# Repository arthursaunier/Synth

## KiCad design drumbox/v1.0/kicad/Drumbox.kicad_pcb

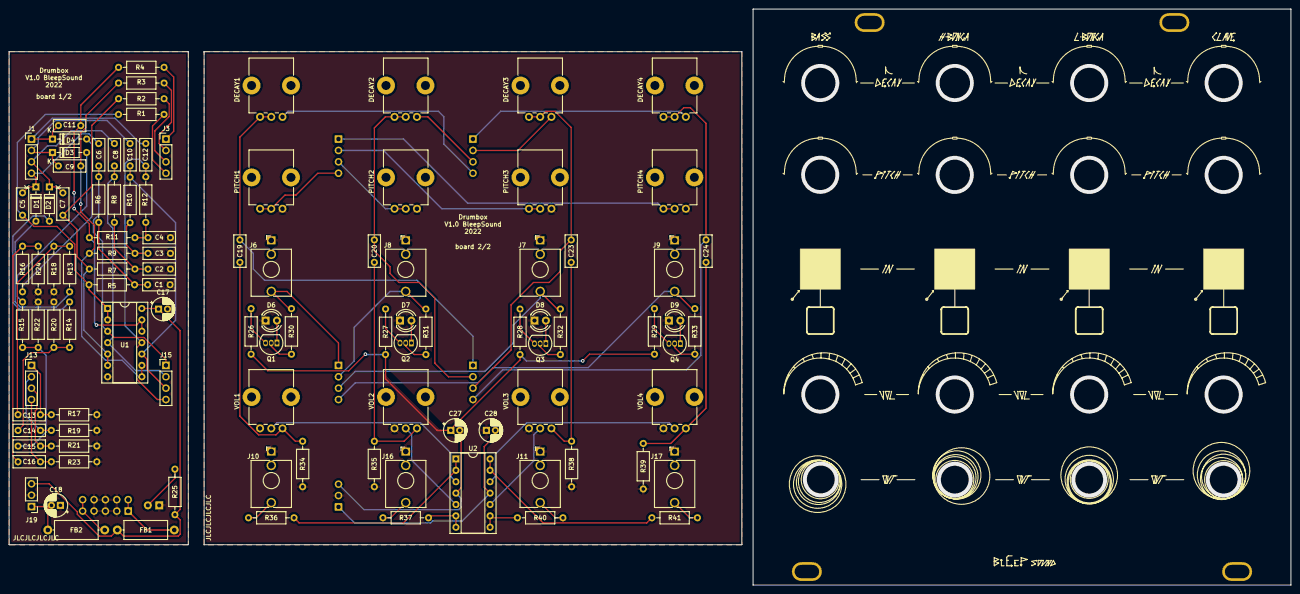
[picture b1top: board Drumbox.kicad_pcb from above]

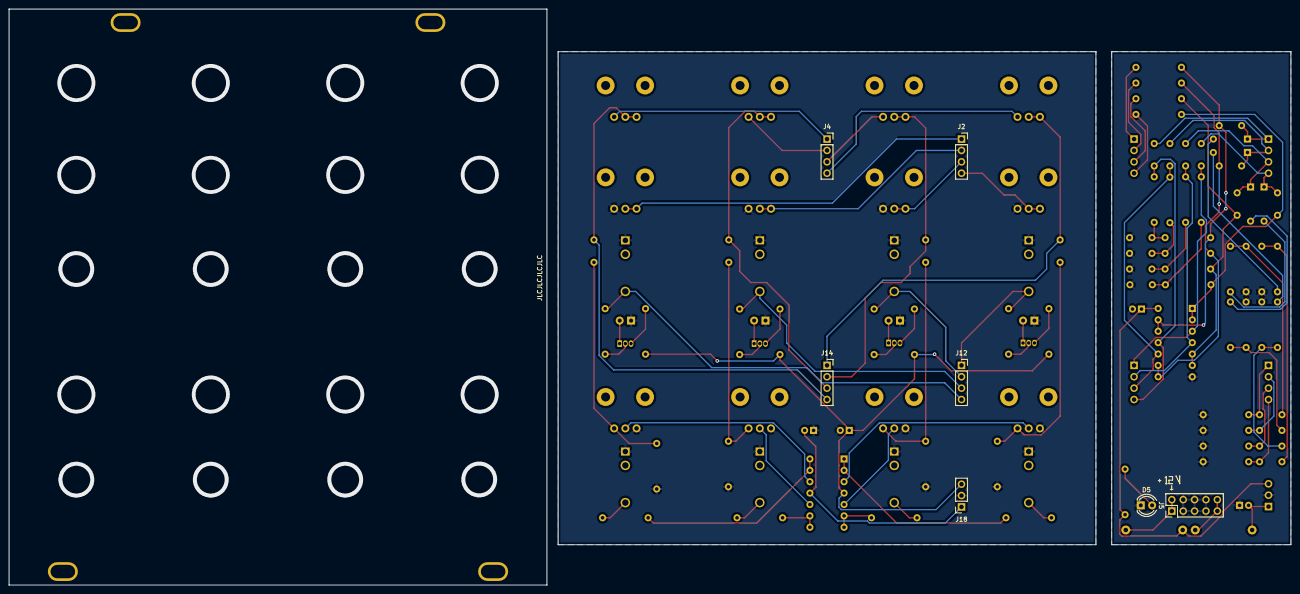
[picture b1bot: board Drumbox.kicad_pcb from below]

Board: 2 copper layers, 286.0 x 128.5 mm, 113 parts (7 on the bottom side), 66 nets.

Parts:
C1, C13: 150nF; C_Disc_D7.0mm_W2.5mm_P5.00mm
C2, C14: 33nF; C_Disc_D7.0mm_W2.5mm_P5.00mm
C3, C15: 39nF; C_Disc_D7.0mm_W2.5mm_P5.00mm
C4: 56nF; C_Disc_D7.0mm_W2.5mm_P5.00mm
C5, C6: 47nF; C_Disc_D7.0mm_W2.5mm_P5.00mm
C7, C8: 10nF; C_Disc_D7.0mm_W2.5mm_P5.00mm
C9, C10: 12nF; C_Disc_D7.0mm_W2.5mm_P5.00mm
C11, C12: 1.5nF; C_Disc_D7.0mm_W2.5mm_P5.00mm
C16: 4.7nF; C_Disc_D7.0mm_W2.5mm_P5.00mm
C17, C18: 10µ; CP_Radial_D5.0mm_P2.00mm
C19, C20, C23, C24: .1µF; C_Disc_D7.0mm_W2.5mm_P5.00mm
C27, C28: 100n; CP_Radial_D5.0mm_P2.00mm
D1, D2, D3, D4: 1N4148; D_DO-35_SOD27_P7.62mm_Horizontal
D5: LED-12V; LED_D4.0mm
D6: LED1; LED_D4.0mm
D7: LED2; LED_D4.0mm
D8: LED3; LED_D4.0mm
D9: LED4; LED_D4.0mm
DECAY1, DECAY2, DECAY3, DECAY4: 470k; Potentiometer_Bourns_PTV09A-1_Single_Vertical
FB1, FB2: 10R; L_Axial_L9.5mm_D4.0mm_P12.70mm_Horizontal_Fastron_SMCC
J1, J3, J13, J15: Conn_01x04_Male; PinHeader_1x04_P2.54mm_Vertical
J2, J4, J12, J14: Conn_01x04_Female; PinSocket_1x04_P2.54mm_Vertical
J5: Power Input; PinHeader_2x05_P2.54mm_Vertical
J6: Bass IN; Jack_3.5mm_QingPu_WQP-PJ398SM_Vertical_CircularHoles
J7: LBonga IN; Jack_3.5mm_QingPu_WQP-PJ398SM_Vertical_CircularHoles
J8: HBonga IN; Jack_3.5mm_QingPu_WQP-PJ398SM_Vertical_CircularHoles
J9: Clave IN; Jack_3.5mm_QingPu_WQP-PJ398SM_Vertical_CircularHoles
J10: Bass OUT; Jack_3.5mm_QingPu_WQP-PJ398SM_Vertical_CircularHoles
J11: LBonga OUT; Jack_3.5mm_QingPu_WQP-PJ398SM_Vertical_CircularHoles
J16: HBonga OUT; Jack_3.5mm_QingPu_WQP-PJ398SM_Vertical_CircularHoles
J17: Clave OUT; Jack_3.5mm_QingPu_WQP-PJ398SM_Vertical_CircularHoles
J18: Conn_01x03_Female; PinSocket_1x03_P2.54mm_Vertical
J19: Conn_01x03_Male; PinHeader_1x03_P2.54mm_Vertical
PITCH1, PITCH2, PITCH3, PITCH4: 10k; Potentiometer_Bourns_PTV09A-1_Single_Vertical
Q1, Q2, Q3, Q4: 2N3904; TO-92_Inline
R1, R2, R3, R4: 150k; R_Axial_DIN0207_L6.3mm_D2.5mm_P10.16mm_Horizontal
R5, R6, R7, R8, R9, R10, R11, R12: 68k; R_Axial_DIN0207_L6.3mm_D2.5mm_P10.16mm_Horizontal
R13, R14, R15, R16: 27k; R_Axial_DIN0207_L6.3mm_D2.5mm_P10.16mm_Horizontal
R17, R19, R21, R23: 12k; R_Axial_DIN0207_L6.3mm_D2.5mm_P10.16mm_Horizontal
R18, R20, R22, R24, R30, R31, R32, R33: 47k; R_Axial_DIN0207_L6.3mm_D2.5mm_P10.16mm_Horizontal
R25: 2.2k; R_Axial_DIN0207_L6.3mm_D2.5mm_P10.16mm_Horizontal
R26, R27, R28, R29, R36, R37, R40, R41: 1k; R_Axial_DIN0207_L6.3mm_D2.5mm_P10.16mm_Horizontal
R34, R35, R38, R39: 1M; R_Axial_DIN0207_L6.3mm_D2.5mm_P10.16mm_Horizontal
U1: 4011; DIP-14_W7.62mm_Socket
U2: TL074; DIP-14_W7.62mm_Socket
VOL1, VOL2, VOL3, VOL4: 10k; Potentiometer_Bourns_PTV09A-1_Single_Vertical

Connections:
+12V: C17.1, C27.1, FB1.1, J18.3, J19.3, R25.1, R26.1, R27.1, R28.1, R29.1, U1.14 (VDD), U2.4 (V+)
-12V: C18.2, C28.2, FB2.1, J18.1, J19.1, U2.11 (V-)
DEIn1: DECAY1.1, J3.4, J4.4, R1.1
DEIn2: DECAY2.1, J3.3, J4.3, R2.1
DEIn3: DECAY3.1, J3.2, J4.2, R3.1
DEIn4: DECAY4.1, J3.1, J4.1, R4.1
GND: C1.2, C2.2, C3.2, C4.2, C17.2, C18.1, C27.2, C28.1, D5.1 (K), D6.1 (K), D7.1 (K), D8.1 (K), D9.1 (K), J5.3, J5.4, J5.5, J5.6, J5.7, J5.8, J6.S, J7.S, J8.S, J9.S, J10.S, J11.S, J16.S, J17.S, J18.2, J19.2, PITCH1.1, PITCH2.1, PITCH3.1, PITCH4.1, R17.2, R18.1, R19.2, R20.1, R21.2, R22.1, R23.2, R24.1, R34.2, R35.2, R38.2, R39.2, U1.7 (VSS), VOL1.3, VOL2.3, VOL3.3, VOL4.3
In1: C13.1, J6.T, J12.1, J13.1, R17.1, R30.1
In2: C14.1, J8.T, J12.2, J13.2, R19.1, R31.1
In3: C15.1, J7.T, J12.3, J13.3, R21.1, R32.1
In4: C16.1, J9.T, J12.4, J13.4, R23.1, R33.1
unnamed: C1.1, R5.1, R6.2
unnamed: C2.1, R7.1, R8.2
unnamed: C3.1, R9.1, R10.2
unnamed: C4.1, R11.1, R12.2
unnamed: C5.1, R1.2, R5.2, U1.1, U1.2
unnamed: C7.1, R2.2, R7.2, U1.5, U1.6
unnamed: C9.1, R3.2, R9.2, U1.8, U1.9
unnamed: C11.1, R4.2, R11.2, U1.12, U1.13
unnamed: C13.2, R13.1, R18.2
unnamed: C14.2, R14.1, R20.2
unnamed: C15.2, R15.1, R22.2
unnamed: C16.2, R16.1, R24.2
unnamed: C19.2, R34.1, VOL1.1
unnamed: C20.2, R35.1, VOL2.1
unnamed: C23.2, R38.1, VOL3.1
unnamed: C24.2, R39.1, VOL4.1
unnamed: D1.2 (A), R13.2
unnamed: D2.2 (A), R14.2
unnamed: D3.2 (A), R15.2
unnamed: D4.2 (A), R16.2
unnamed: D5.2 (A), R25.2
unnamed: D6.2 (A), Q1.1 (E)
unnamed: D7.2 (A), Q2.1 (E)
unnamed: D8.2 (A), Q3.1 (E)
unnamed: D9.2 (A), Q4.1 (E)
unnamed: FB1.2, J5.1, J5.2
unnamed: FB2.2, J5.9, J5.10
unnamed: Q1.2 (B), R30.2
unnamed: Q1.3 (C), R26.2
unnamed: Q2.2 (B), R31.2
unnamed: Q2.3 (C), R27.2
unnamed: Q3.2 (B), R32.2
unnamed: Q3.3 (C), R28.2
unnamed: Q4.2 (B), R33.2
unnamed: Q4.3 (C), R29.2
unnamed: R36.2, U2.1, U2.2 (-)
unnamed: R37.2, U2.6 (-), U2.7
unnamed: R40.2, U2.8, U2.9 (-)
unnamed: R41.2, U2.13 (-), U2.14
unnamed: U2.3 (+), VOL1.2
unnamed: U2.5 (+), VOL2.2
unnamed: U2.10 (+), VOL3.2
unnamed: U2.12 (+), VOL4.2
O1: C6.2, C19.1, DECAY1.2, DECAY1.3, J14.1, J15.1, R6.1, U1.3
O2: C8.2, C20.1, DECAY2.2, DECAY2.3, J14.2, J15.2, R8.1, U1.4
O3: C10.2, C23.1, DECAY3.2, DECAY3.3, J14.3, J15.3, R10.1, U1.10
O4: C12.2, C24.1, DECAY4.2, DECAY4.3, J14.4, J15.4, R12.1, U1.11
Out1: J10.T, R36.1
Out2: J16.T, R37.1
Out3: J11.T, R40.1
Out4: J17.T, R41.1
PIOut1: C5.2, C6.1, D1.1 (K), J1.4, J2.4, PITCH1.2, PITCH1.3
PIOut2: C7.2, C8.1, D2.1 (K), J1.3, J2.3, PITCH2.2, PITCH2.3
PIOut3: C9.2, C10.1, D3.1 (K), J1.2, J2.2, PITCH3.2, PITCH3.3
PIOut4: C11.2, C12.1, D4.1 (K), J1.1, J2.1, PITCH4.2, PITCH4.3

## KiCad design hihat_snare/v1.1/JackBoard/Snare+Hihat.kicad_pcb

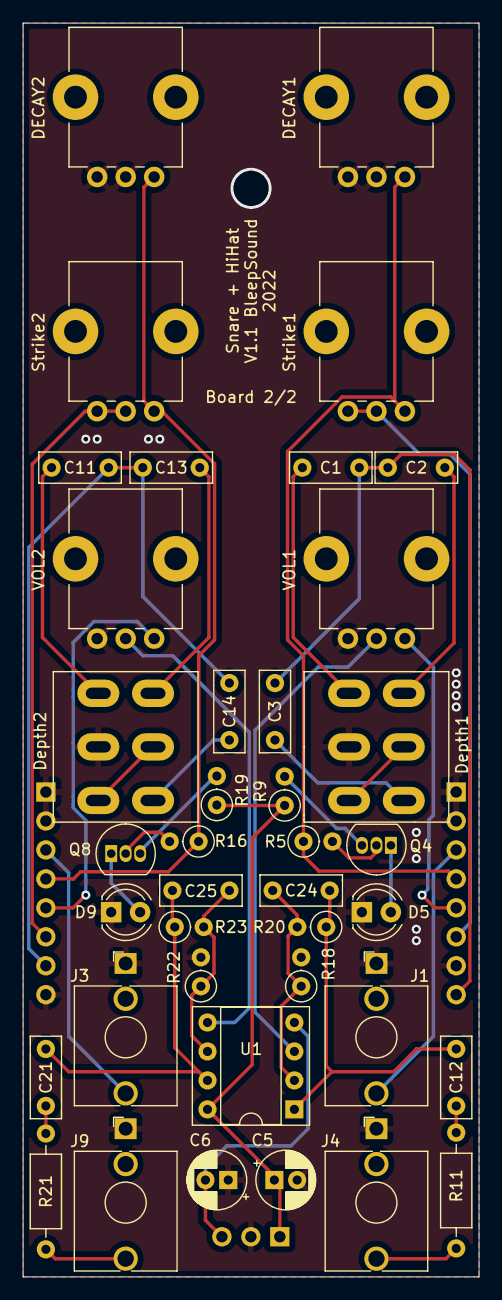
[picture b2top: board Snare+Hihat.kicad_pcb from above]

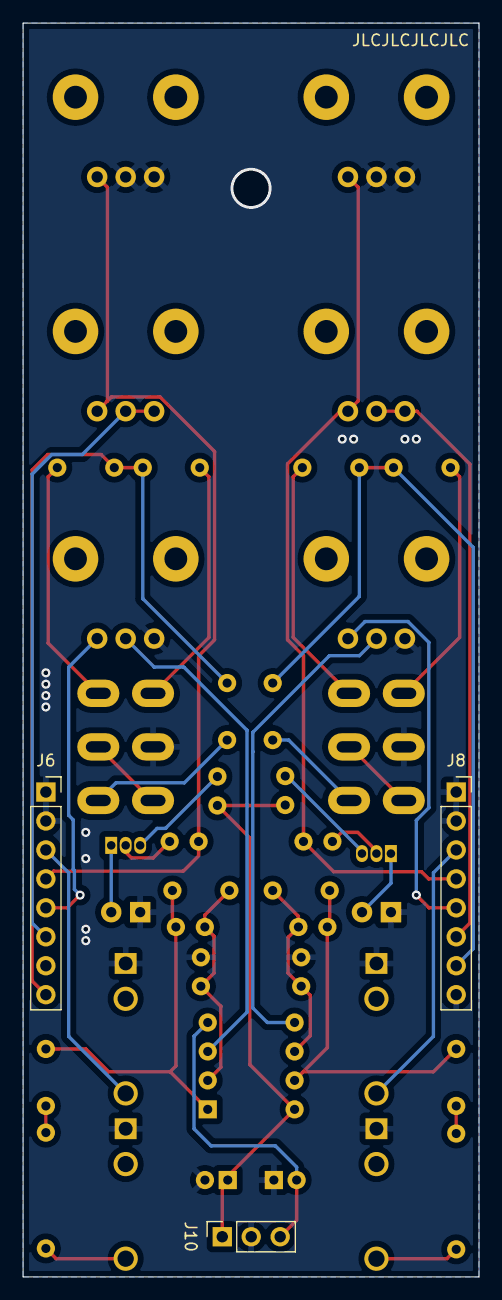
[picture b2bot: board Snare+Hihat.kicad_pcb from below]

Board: 2 copper layers, 40.0 x 110.0 mm, 42 parts (3 on the bottom side), 37 nets.

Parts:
C1, C11, C12, C21: 10µF; C_Disc_D7.0mm_W2.5mm_P5.00mm
C2, C13: 1µF; C_Disc_D7.0mm_W2.5mm_P5.00mm
C3, C14: 0.1µF; C_Disc_D7.0mm_W2.5mm_P5.00mm
C5, C6: 10µ; CP_Radial_D5.0mm_P2.00mm
C24, C25: 22pF; C_Disc_D7.0mm_W2.5mm_P5.00mm
D5: Trig Snare; LED_D4.0mm
D9: Trig_HiHat; LED_D4.0mm
DECAY1, DECAY2: 100k; Pot-bourns-alpha
Depth1, Depth2: SW_Push_DPDT; SW_DPDT_Toggle
J1: Snare IN; Thonkiconn
J3: HiHat IN; Thonkiconn
J4: Snare OUT; Thonkiconn
J6, J8: Conn_01x08_Female; PinSocket_1x08_P2.54mm_Vertical
J9: HiHat OUT; Thonkiconn
J10: Conn_01x03_Female; PinSocket_1x03_P2.54mm_Vertical
Q4, Q8: 2N3904; TO-92_Inline
R5, R16: 100k; R_Axial_DIN0207_L6.3mm_D2.5mm_P2.54mm_Vertical
R9, R19: 1k; R_Axial_DIN0207_L6.3mm_D2.5mm_P2.54mm_Vertical
R11, R21: 1k; R_Axial_DIN0207_L6.3mm_D2.5mm_P10.16mm_Horizontal
R18, R22: 10k; R_Axial_DIN0207_L6.3mm_D2.5mm_P2.54mm_Vertical
R20, R23: 330k; R_Axial_DIN0207_L6.3mm_D2.5mm_P2.54mm_Vertical
Strike1, Strike2: 100k; Pot-bourns-alpha
U1: TL072; DIP-8_W7.62mm_Socket
VOL1, VOL2: 10k; Pot-bourns-alpha

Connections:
+12V: C5.1, J10.1, R9.1, R19.1, U1.8 (V+)
-12V: C6.2, J10.3, U1.4 (V-)
/DeH: C1.1, C2.1, C3.1, J6.8
/HiDH: C11.1, C13.1, C14.1, J8.7
/HiH: DECAY2.1, J8.4, R16.1, Strike2.1
/HiI: J3.T, J8.3
/HiO: J8.5, VOL2.1
/Ho: J8.6, Strike2.2, Strike2.3
/SnH: DECAY1.1, J6.4, R5.1, Strike1.1
/SnI: J1.T, J6.3
/SnO: J6.5, VOL1.1
/So: J6.6, Strike1.2, Strike1.3
GND: C5.2, C6.1, D5.1 (K), D9.1 (K), DECAY1.2, DECAY1.3, DECAY2.2, DECAY2.3, Depth1.2 (B), Depth2.2 (B), J1.S, J3.S, J4.S, J6.1, J6.2, J6.7, J8.1, J8.2, J8.8, J9.S, J10.2, R18.2, R22.2, VOL1.3, VOL2.3
unnamed: C1.2, Depth1.1 (A)
unnamed: C2.2, Depth1.4 (A)
unnamed: C3.2, Depth1.6 (C)
unnamed: C11.2, Depth2.1 (A)
unnamed: C12.1, C24.2, R20.1, U1.1
unnamed: C12.2, R11.2
unnamed: C13.2, Depth2.4 (A)
unnamed: C14.2, Depth2.6 (C)
unnamed: C21.1, C25.2, R23.1, U1.7
unnamed: C21.2, R21.2
unnamed: D5.2 (A), Q4.1 (E)
unnamed: D9.2 (A), Q8.1 (E)
unnamed: Depth1.3 (C), Depth1.5 (B)
unnamed: Depth2.3 (C), Depth2.5 (B)
unnamed: J4.T, R11.1
unnamed: J9.T, R21.1
unnamed: Q4.2 (B), R5.2
unnamed: Q4.3 (C), R9.2
unnamed: Q8.2 (B), R16.2
unnamed: Q8.3 (C), R19.2
unnamed: C24.1, R18.1, R20.2, U1.2 (-)
unnamed: U1.3 (+), VOL1.2
unnamed: U1.5 (+), VOL2.2
unnamed: C25.1, R22.1, R23.2, U1.6 (-)

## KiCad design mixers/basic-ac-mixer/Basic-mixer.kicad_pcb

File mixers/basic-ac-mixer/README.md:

---
permalink: /mixers/basic-ac-mixer/index.html
layout: single
---

# Basic DC mixer

[See bom](bom/ibom.html)

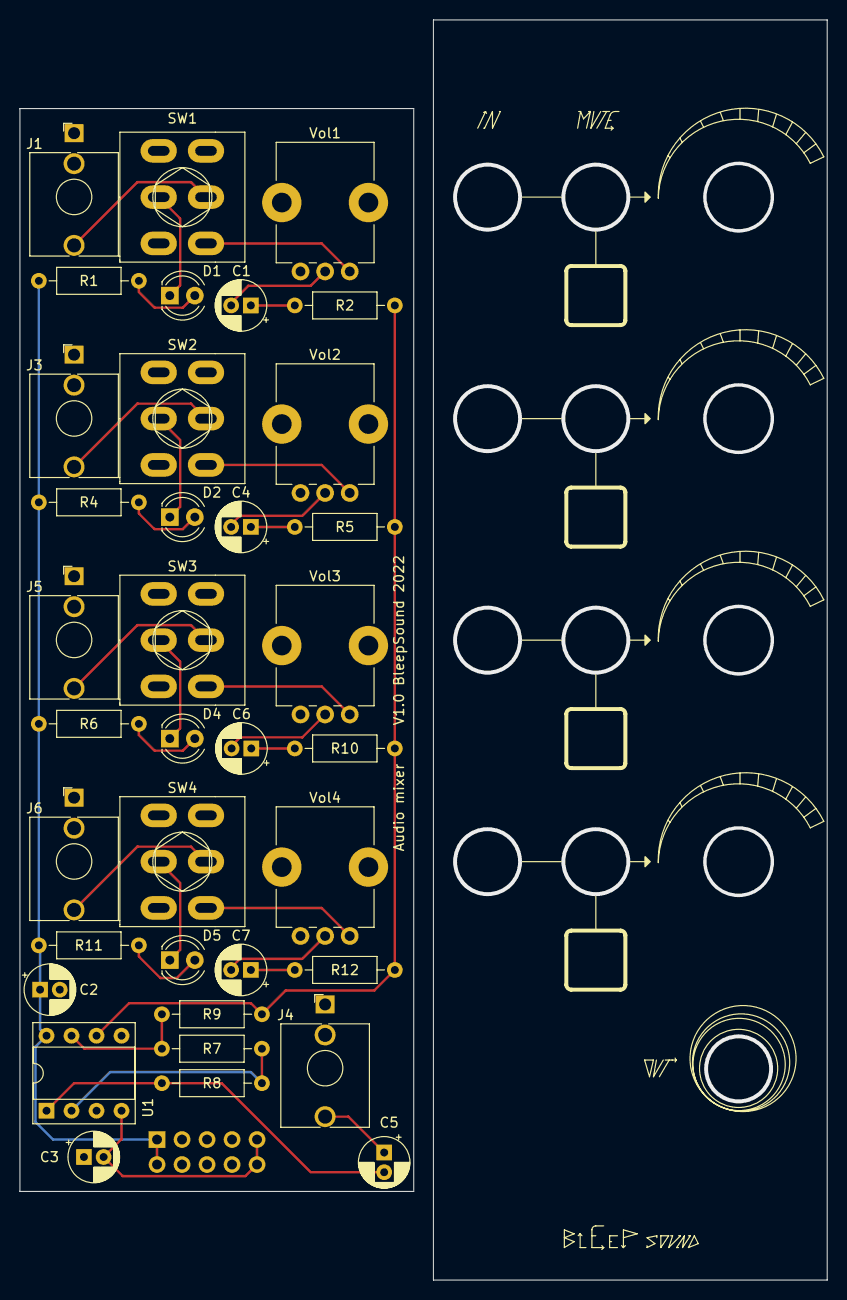
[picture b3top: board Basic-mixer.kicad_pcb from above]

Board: 2 copper layers, 82.0 x 128.0 mm, 37 parts (1 on the bottom side), 32 nets.

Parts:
C1, C4, C6, C7: .1µF; CP_Radial_D5.0mm_P2.00mm
C2, C3: 10µ; CP_Radial_D5.0mm_P2.00mm
C5: 10µF; CP_Radial_D5.0mm_P2.00mm
D1, D2, D4, D5: LED-mute; LED_D4.0mm
J1, J3, J5, J6: In; Thonkiconn
J2: Power Input; PinHeader_2x05_P2.54mm_Vertical
J4: Out; Thonkiconn
R1, R4, R6, R11: 4.7k; R_Axial_DIN0207_L6.3mm_D2.5mm_P10.16mm_Horizontal
R2, R5, R9, R10, R12: 100k; R_Axial_DIN0207_L6.3mm_D2.5mm_P10.16mm_Horizontal
R7, R8: 10k; R_Axial_DIN0207_L6.3mm_D2.5mm_P10.16mm_Horizontal
SW1, SW2, SW3, SW4: Mute; SW_DPDT_Toggle
U1: TL072; DIP-8_W7.62mm_Socket
Vol1, Vol2, Vol3, Vol4: 10k; Pot-bourns-alpha

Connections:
+12V: C2.1, J2.1, J2.2, R1.1, R4.1, R6.1, R11.1, U1.8 (V+)
-12V: C3.2, J2.9, J2.10, U1.4 (V-)
GND: C2.2, C3.1, J1.S, J2.3, J2.4, J2.5, J2.6, J2.7, J2.8, J3.S, J4.S, J5.S, J6.S, SW1.1 (A), SW2.1 (A), SW3.1 (A), SW4.1 (A), U1.3 (+), U1.5 (+), Vol1.3, Vol2.3, Vol3.3, Vol4.3
unnamed: C1.1, R2.2
unnamed: C1.2, Vol1.2
unnamed: C4.1, R5.2
unnamed: C4.2, Vol2.2
unnamed: C5.1, J4.T
unnamed: C5.2, R8.1, U1.1
unnamed: C6.1, R10.2
unnamed: C6.2, Vol3.2
unnamed: C7.1, R12.2
unnamed: C7.2, Vol4.2
unnamed: D1.1 (K), SW1.2 (B)
unnamed: D1.2 (A), R1.2
unnamed: D2.1 (K), SW2.2 (B)
unnamed: D2.2 (A), R4.2
unnamed: D4.1 (K), SW3.2 (B)
unnamed: D4.2 (A), R6.2
unnamed: D5.1 (K), SW4.2 (B)
unnamed: D5.2 (A), R11.2
unnamed: J1.T, SW1.5 (B)
unnamed: J3.T, SW2.5 (B)
unnamed: J5.T, SW3.5 (B)
unnamed: J6.T, SW4.5 (B)
unnamed: R7.1, R8.2, U1.2 (-)
unnamed: R7.2, R9.1, U1.7
unnamed: R2.1, R5.1, R9.2, R10.1, R12.1, U1.6 (-)
unnamed: SW1.6 (C), Vol1.1
unnamed: SW2.6 (C), Vol2.1
unnamed: SW3.6 (C), Vol3.1
unnamed: SW4.6 (C), Vol4.1
